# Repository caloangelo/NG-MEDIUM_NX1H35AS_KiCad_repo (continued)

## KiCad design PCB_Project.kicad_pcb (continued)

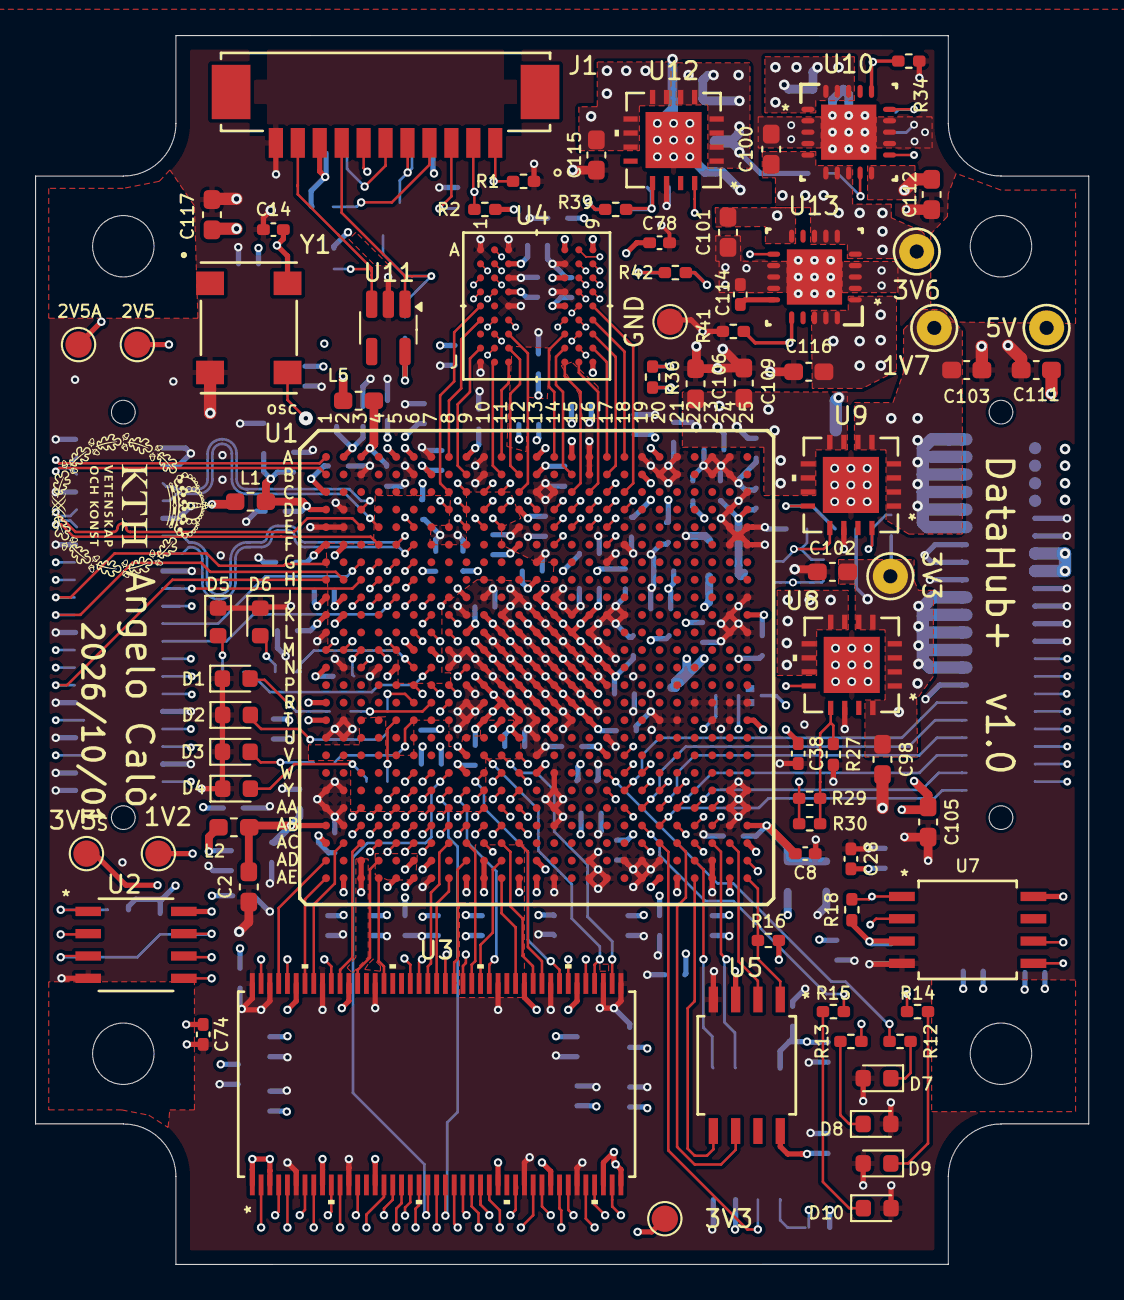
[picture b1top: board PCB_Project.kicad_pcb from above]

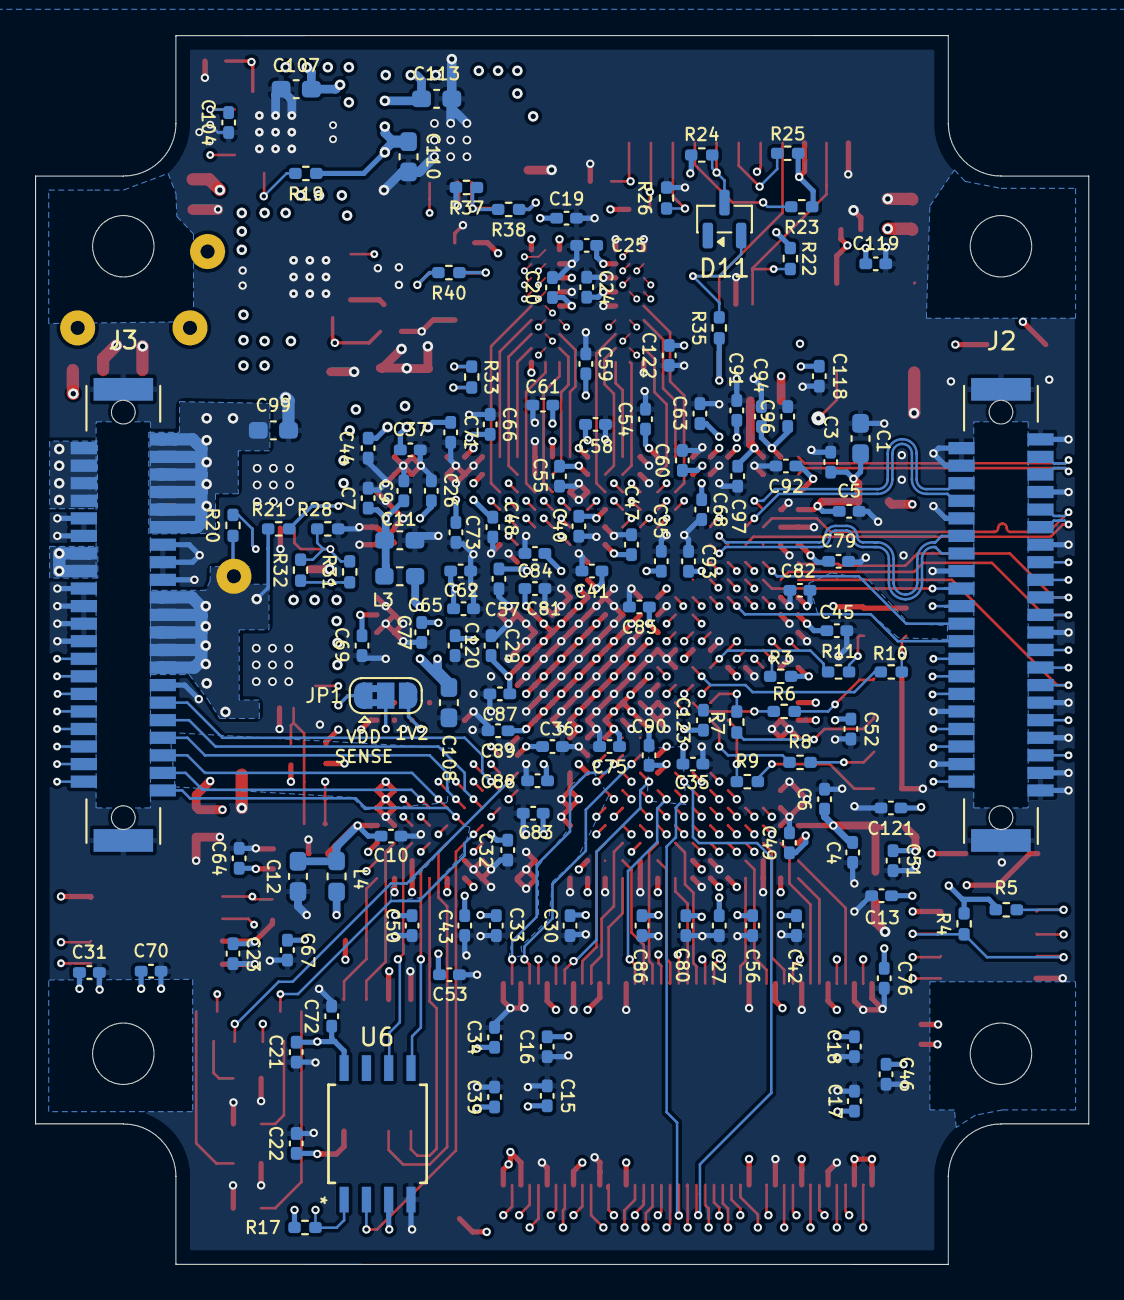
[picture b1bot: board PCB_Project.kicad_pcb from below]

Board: 8 copper layers, 60.0 x 70.0 mm, 209 parts (135 on the bottom side), 210 nets.

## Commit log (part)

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2026-06-23 Project start
    started to take track of changes since major changes will occur in the future.
2026-06-29 first iteration of sdram
    Fanout completed, started tracing towards the chip
2026-06-29 iteration 2 sdram
    finished connections with sdram. shortened and adjusted as much as possible the traces.
    straightened the traces.
2026-06-29 SDRAM iteration 3
    finalized SDRAM connections and placement. optimized space and connectivity.
    TBD:
    iteration 4 will be regarding a reconfiguration of the pinout to try out a more optimal tracing.
